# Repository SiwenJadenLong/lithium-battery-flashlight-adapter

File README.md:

# lithium-battery-flashlight-adapter
Design that uses a custom pcb and 3D printing for converting a powerful surge brand flashlight powered by 6 AA batteries for 9v to a rechargable 26650 with usb-c charging.

Why?:
I don't like AA batteries :P
and I need a bright flashflight when I'm skating home at night

Original Flashlight  page:
https://www.tractorsupply.com/tsc/product/surge-1-000-lumen-tactical-led-alkaline-flashlight-hhl3060as 

26650 Battery in interest:
https://www.18650batterystore.com/products/sinowatt-70hp-26650-7000mah-14a-battery

Digikey parts list:
https://www.digikey.com/en/mylists/list/EGW4OOC67G

# Plan:
1.  (WE ARE HERE) Create a circular pcb that boosts battery voltage to 9v and allows for usb-c recharging, does not have to do both at the same time. 
2. Create 3D printing casing for adapter
3. assemble
4. profit?

PCB V1:

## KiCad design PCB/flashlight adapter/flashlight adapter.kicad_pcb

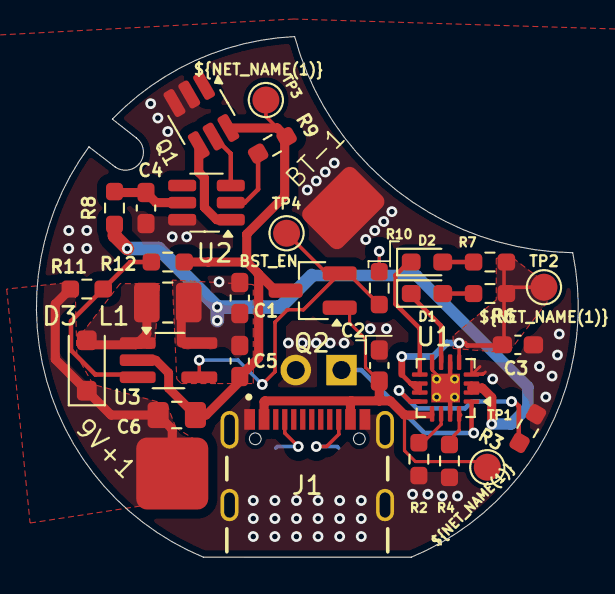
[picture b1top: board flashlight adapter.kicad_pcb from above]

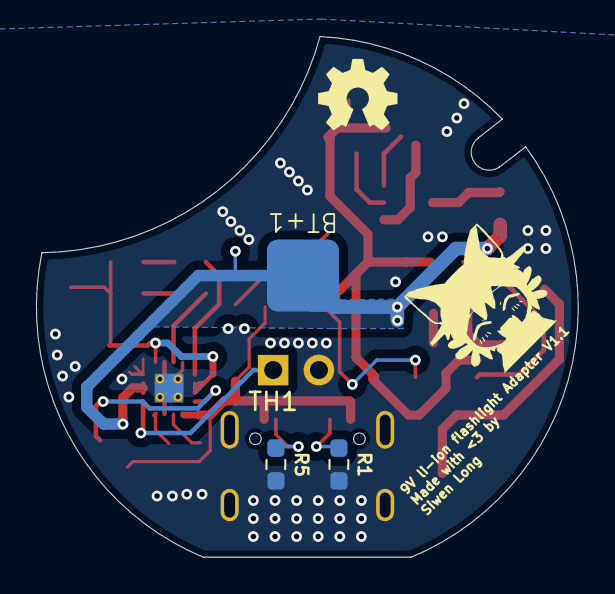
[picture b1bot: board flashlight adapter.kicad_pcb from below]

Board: 2 copper layers, 30.1 x 28.9 mm, 36 parts (4 on the bottom side), 23 nets.

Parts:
9V+1: 9V; 4mm_by_4mm_pad
BT+1: BATT+; 4mm_by_4mm_pad
BT-1: BATT-; 3mm_by_4mm_pad
C1, C3, C5: 4.7 uF; C_0603_1608Metric_Pad1.08x0.95mm_HandSolder
C2: 1uF; C_0603_1608Metric_Pad1.08x0.95mm_HandSolder
C4: 0.1uF; C_0603_1608Metric_Pad1.08x0.95mm_HandSolder
C6: 10uF; C_0805_2012Metric_Pad1.18x1.45mm_HandSolder
D1: RED; LED_0603_1608Metric_Pad1.05x0.95mm_HandSolder
D2: GREEN; LED_0603_1608Metric_Pad1.05x0.95mm_HandSolder
D3: D_Schottky; D_SOD-123F
J1: USB4105-GF-A; GCT_USB4105-GF-A
L1: 4.7uH; L_1008_2520Metric_Pad1.43x2.20mm_HandSolder
Q1: FS8205A; SOT-23-6_Handsoldering
Q2: Q_NMOS_GSD; SOT-23_Handsoldering
R1, R5, R10: 10k; R_0603_1608Metric_Pad0.98x0.95mm_HandSolder
R2: 51k; R_0603_1608Metric_Pad0.98x0.95mm_HandSolder
R3: 1.1kΩ; R_0603_1608Metric_Pad0.98x0.95mm_HandSolder
R4: 590Ω; R_0603_1608Metric_Pad0.98x0.95mm_HandSolder
R6, R7: 120Ω; R_0603_1608Metric_Pad0.98x0.95mm_HandSolder
R8: 470Ω; R_0603_1608Metric_Pad0.98x0.95mm_HandSolder
R9: 2kΩ; R_0603_1608Metric_Pad0.98x0.95mm_HandSolder
R11: 28k; R_0603_1608Metric_Pad0.98x0.95mm_HandSolder
R12: 4.3k; R_0603_1608Metric_Pad0.98x0.95mm_HandSolder
TH1: 10K; PinHeader_1x02_P2.54mm_Vertical
TP1: VBUS; TestPoint_Pad_D1.5mm
TP2: OUT; TestPoint_Pad_D1.5mm
TP3: P+ & BATT+; TestPoint_Pad_D1.5mm
TP4: BST EN; TestPoint_Pad_D1.5mm
U1: BQ24074RGT; VQFN-16-1EP_3x3mm_P0.5mm_EP1.6x1.6mm_ThermalVias
U2: DW01A; SOT-23-6_Handsoldering
U3: MIC2295YD5-TR; TSOT-23-5_HandSoldering

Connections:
/BAT: BT+1.1, C1.1, C5.1, L1.1, R8.1, R10.1, U1.2 (BAT), U1.3 (BAT), U3.5 (VIN)
/EN2: C3.1, R6.2, R7.2, TP2.1, U1.5 (EN2), U1.10 (OUT), U1.11 (OUT)
/P-: C5.2, C6.2, Q1.6, Q2.3 (S), R9.2, R12.2, TP3.1, U3.2 (GND)
/TS: TH1.1, U1.1 (TS)
/VBUS: C2.1, J1.A4_B9 (VBUS), J1.B4_A9 (VBUS__1), Q2.1 (G), TP1.1, U1.13 (IN)
GND: BT-1.1, C1.2, C2.2, C3.2, C4.2, J1.A1_B12 (GND), J1.B1_A12 (GND__1), J1.SH1 (SHELL_GND), J1.SH2 (SHELL_GND__1), J1.SH3 (SHELL_GND__2), J1.SH4 (SHELL_GND__3), Q1.2, Q1.3, R1.2, R2.2, R3.2, R4.2, R5.2, TH1.2, U1.4 (~CE), U1.6 (EN1), U1.8 (VSS), U1.15 (ITERM), U1.17 (VSS), U2.6 (GND)
unnamed: D1.2 (A), R6.1
unnamed: D1.1 (K), U1.7 (~PGOOD)
unnamed: D2.2 (A), R7.1
unnamed: D2.1 (K), U1.9 (~CHG)
unnamed: D3.2 (A), L1.2, U3.1 (SW)
unnamed: 9V+1.1, C6.1, D3.1 (K), R11.1
unnamed: J1.A5 (CC1), R1.1
unnamed: J1.B5 (CC2), R5.1
unnamed: Q2.2 (D), R10.2, TP4.1, U3.4 (EN)
unnamed: R3.1, U1.12 (ILIM)
unnamed: R4.1, U1.16 (ISET)
unnamed: R2.1, U1.14 (TMR)
unnamed: R9.1, U2.2 (CS)
unnamed: Q1.5, U2.3 (OC)
unnamed: Q1.4, U2.1 (OD)
unnamed: C4.1, R8.2, U2.5 (VCC)
unnamed: R11.2, R12.1, U3.3 (FB)

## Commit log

2025-12-29 intro plan written down
2026-01-03 added flowchart, picked out components, started pcb design
2026-01-03 Added Design Notes
2026-01-04 Completed Charging IC schematic
2026-01-04 finished low voltage cutoff ic
2026-01-04 almost completed boast converter, waiting on inductor resistor feedback
2026-01-04 Pretty much finished schematic
2026-01-04 Intial layout complete with DRC, test pads to be added
2026-01-05 Added Boost off when charging
2026-03-13 Fixed usb switch mosfet footprint, sent out second order
2026-03-13 Adjusted Silkscreen to say v1.1
